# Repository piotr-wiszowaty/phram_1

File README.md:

phram\_1
========

phram\_1 is a Commodore Amiga A600 extension - 8 MB of fast RAM.

Features :
----------

* based on modern parts (CoolRunner CPLD, SDRAM)
* PCMCIA-friendly: holding `reset` for more than 3 seconds turns off high 4 MB
* current consumption around 110 mA
* speedup relative to stock A600: 33 % (by SysInfo)
* successfully tested with CheckMem and MemCheck 1.2 (both available
  on [Aminet](http://aminet.net)).

Sources
-------

`cpld/` - MMU design files (Xilinx ISE 14.7)

`pcb/`  - PCB design files (KiCAD, built 2017-11-24 revision a01d81e4b)

`prod/` - JED, Gerbers and a photo of the expansion; the current PCB
          has some tweaks compared with the device on the photo

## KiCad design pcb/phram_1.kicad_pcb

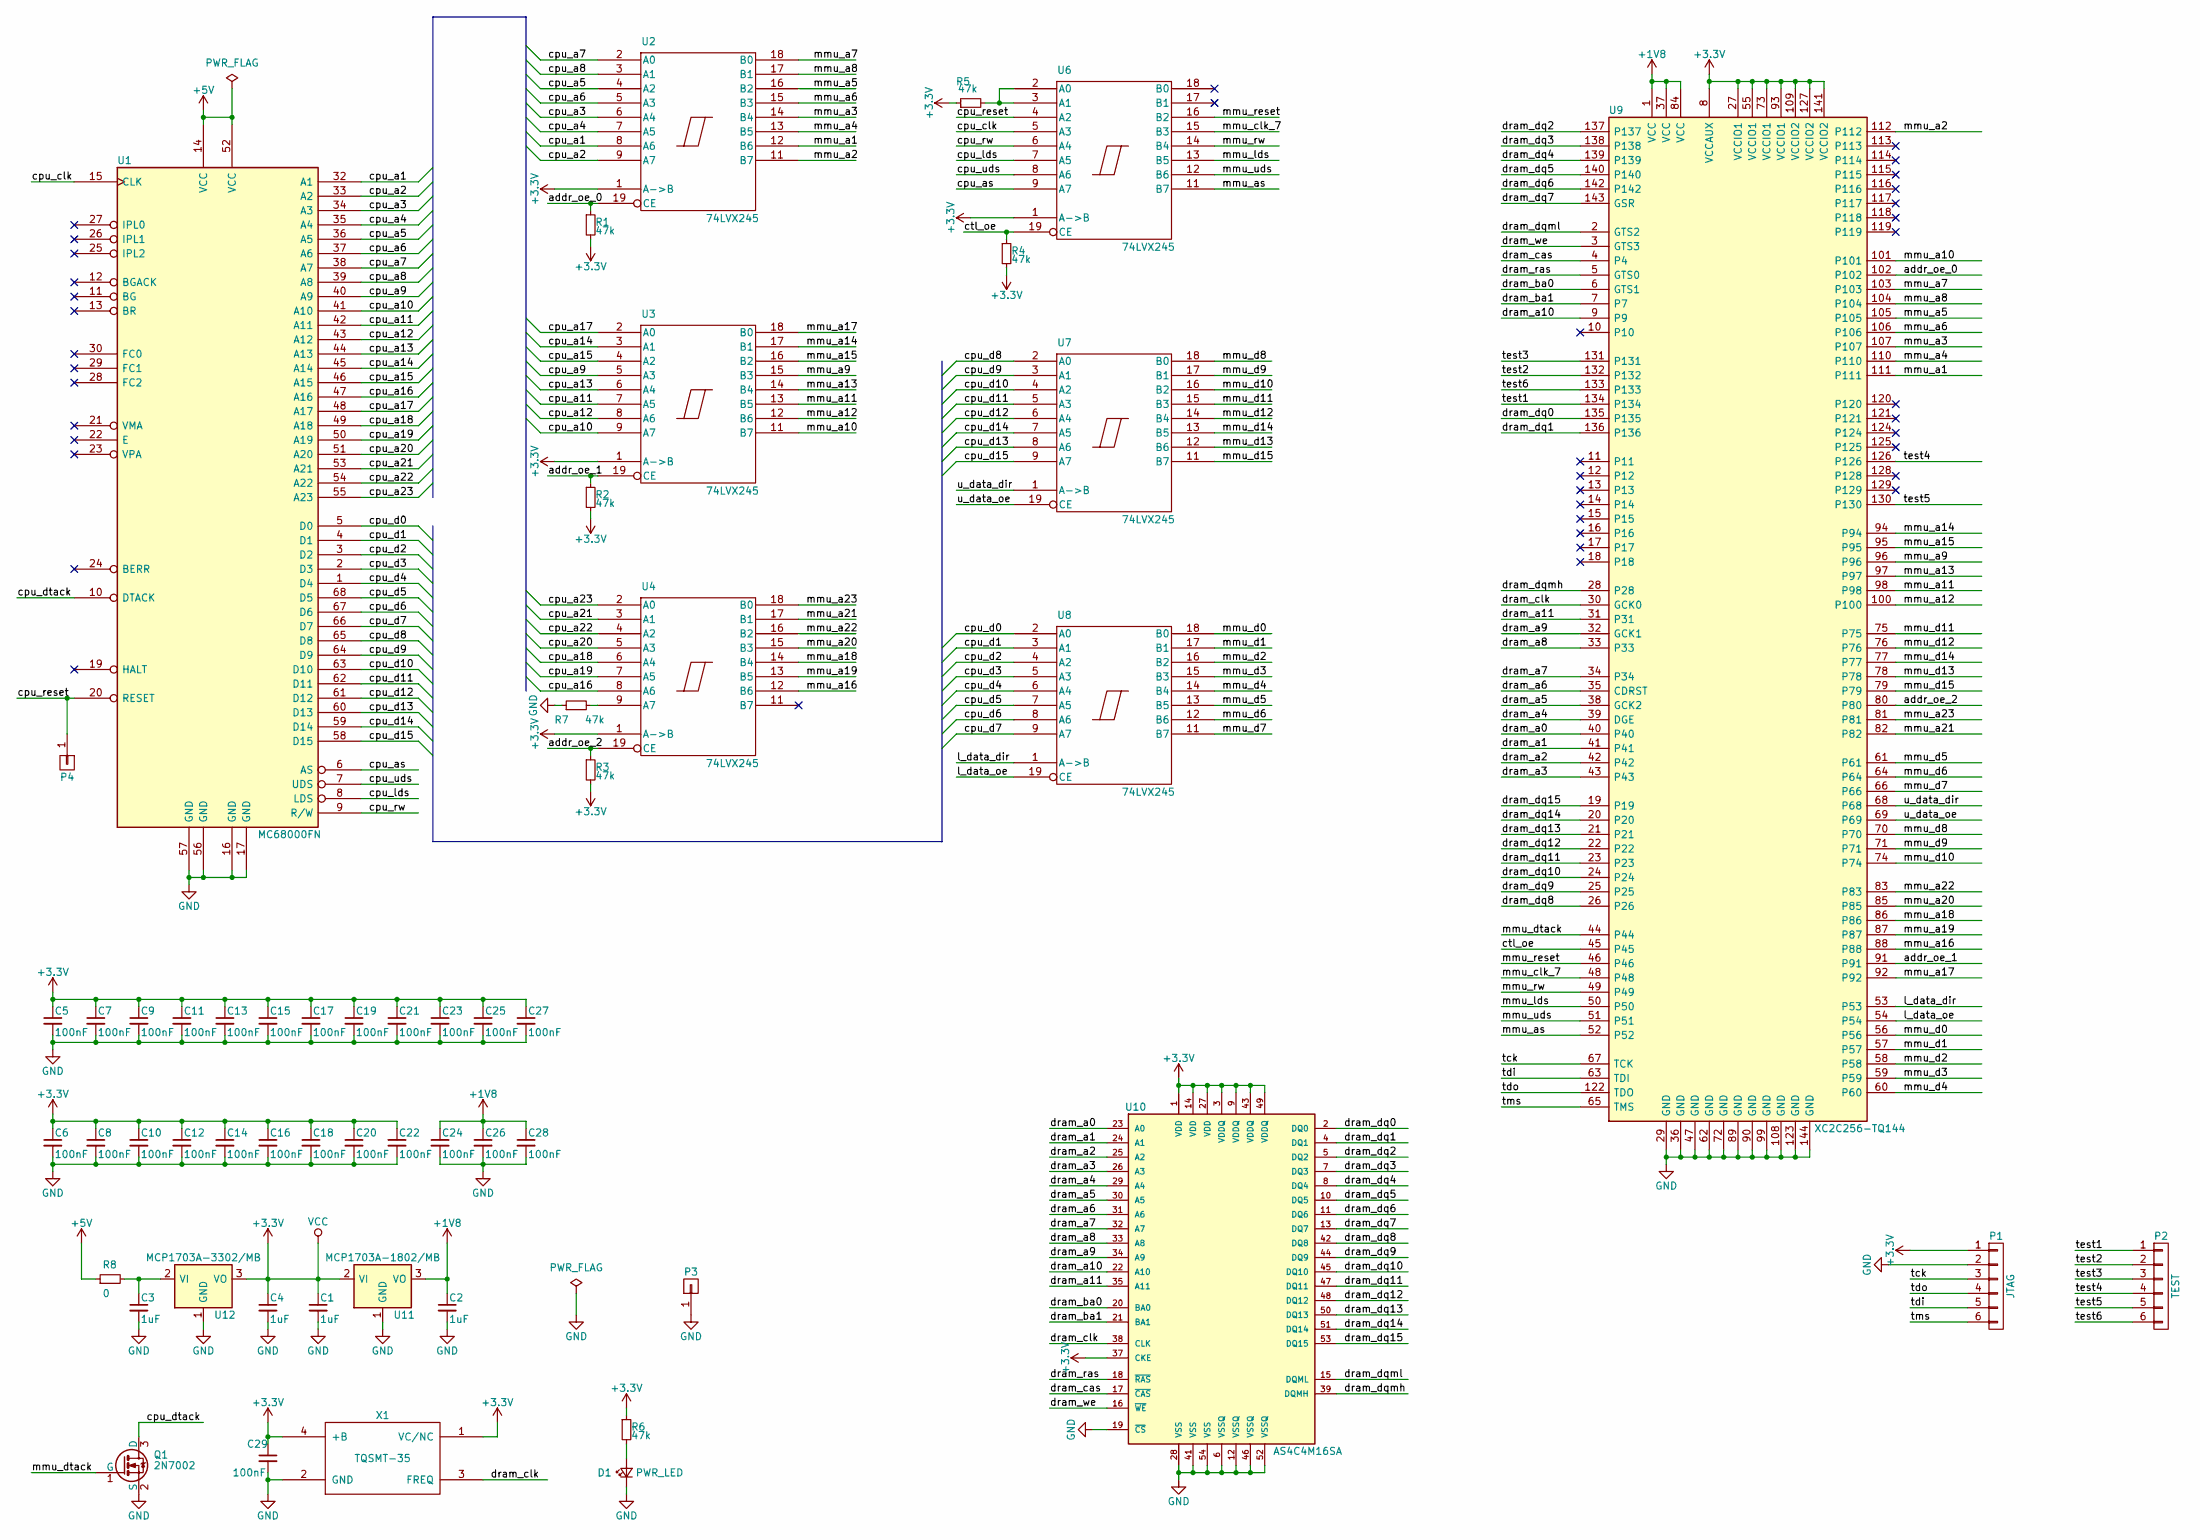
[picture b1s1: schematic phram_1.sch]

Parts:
C1, C2, C3, C4: 1uF; C_1206_HandSoldering
C5, C6, C7, C8, C9, C10, C11, C12, C13, C14, C15, C16, C17, C18, C19, C20, C21, C22, C23, C24, C25, C26, C27, C28, C29: 100nF; C_0805_HandSoldering
D1: PWR_LED; R_0805_HandSoldering
P1: JTAG; Pin_Header_Angled_1x06
P2: TEST; Pin_Header_Angled_1x06
P3, P4: CONN_01X01; Pin_Header_Straight_1x01
Q1: 2N7002; SOT-23
R1, R2, R3, R4, R5, R6, R7: 47k; R_0805_HandSoldering
R8: 0; R_1206_HandSoldering
U1: MC68000FN; PLCC68-upsidedown
U2, U3, U4, U6, U7, U8: 74LVX245; TSSOP-20_4.4x6.5mm_Pitch0.65mm
U9: XC2C256-TQ144; TQFP-144_20x20mm_Pitch0.5mm
U10: AS4C4M16SA; TSOP-II-54_22.22x10.16mm_Pitch0.8mm
U11: MCP1703A-1802/MB; SOT89-3_Housing
U12: MCP1703A-3302/MB; SOT89-3_Housing
X1: TQSMT-35; IS92

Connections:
+1V8: C2.1, C24.1, C26.1, C28.1, U9.1 (VCC), U9.37 (VCC), U9.84 (VCC), U11.3 (VO)
+3V3: C1.1, C4.1, C5.1, C6.1, C7.1, C8.1, C9.1, C10.1, C11.1, C12.1, C13.1, C14.1, C15.1, C16.1, C17.1, C18.1, C19.1, C20.1, C21.1, C22.1, C23.1, C25.1, C27.1, C29.1, P1.1, R1.2, R2.2, R3.2, R4.2, R5.1, R6.1, U2.1 (A->B), U2.20 (VCC), U3.1 (A->B), U3.20 (VCC), U4.1 (A->B), U4.20 (VCC), U6.1 (A->B), U6.20 (VCC), U7.20 (VCC), U8.20 (VCC), U9.8 (VCCAUX), U9.27 (VCCIO1), U9.55 (VCCIO1), U9.73 (VCCIO1), U9.93 (VCCIO1), U9.109 (VCCIO2), U9.127 (VCCIO2), U9.141 (VCCIO2), U10.1 (VDD), U10.3 (VDDQ), U10.9 (VDDQ), U10.14 (VDD), U10.27 (VDD), U10.37 (CKE), U10.43 (VDDQ), U10.49 (VDDQ), U11.2 (VI), U12.3 (VO), X1.1 (VC/NC), X1.4 (+B)
+5V: R8.1, U1.14 (VCC), U1.52 (VCC)
/addr_oe_0: R1.1, U2.19 (CE), U9.102
/addr_oe_1: R2.1, U3.19 (CE), U9.91
/addr_oe_2: R3.1, U4.19 (CE), U9.80
/cpu_a1: U1.32 (A1), U2.8 (A6)
/cpu_a2: U1.33 (A2), U2.9 (A7)
/cpu_a3: U1.34 (A3), U2.6 (A4)
/cpu_a4: U1.35 (A4), U2.7 (A5)
/cpu_a5: U1.36 (A5), U2.4 (A2)
/cpu_a6: U1.37 (A6), U2.5 (A3)
/cpu_a7: U1.38 (A7), U2.2 (A0)
/cpu_a8: U1.39 (A8), U2.3 (A1)
/cpu_a9: U1.40 (A9), U3.5 (A3)
/cpu_a10: U1.41 (A10), U3.9 (A7)
/cpu_a11: U1.42 (A11), U3.7 (A5)
/cpu_a12: U1.43 (A12), U3.8 (A6)
/cpu_a13: U1.44 (A13), U3.6 (A4)
/cpu_a14: U1.45 (A14), U3.3 (A1)
/cpu_a15: U1.46 (A15), U3.4 (A2)
/cpu_a16: U1.47 (A16), U4.8 (A6)
/cpu_a17: U1.48 (A17), U3.2 (A0)
/cpu_a18: U1.49 (A18), U4.6 (A4)
/cpu_a19: U1.50 (A19), U4.7 (A5)
/cpu_a20: U1.51 (A20), U4.5 (A3)
/cpu_a21: U1.53 (A21), U4.3 (A1)
/cpu_a22: U1.54 (A22), U4.4 (A2)
/cpu_a23: U1.55 (A23), U4.2 (A0)
/cpu_as: U1.6 (AS), U6.9 (A7)
/cpu_clk: U1.15 (CLK), U6.5 (A3)
/cpu_d0: U1.5 (D0), U8.2 (A0)
/cpu_d1: U1.4 (D1), U8.3 (A1)
/cpu_d2: U1.3 (D2), U8.4 (A2)
/cpu_d3: U1.2 (D3), U8.5 (A3)
/cpu_d4: U1.1 (D4), U8.6 (A4)
/cpu_d5: U1.68 (D5), U8.7 (A5)
/cpu_d6: U1.67 (D6), U8.8 (A6)
/cpu_d7: U1.66 (D7), U8.9 (A7)
/cpu_d8: U1.65 (D8), U7.2 (A0)
/cpu_d9: U1.64 (D9), U7.3 (A1)
/cpu_d10: U1.63 (D10), U7.4 (A2)
/cpu_d11: U1.62 (D11), U7.5 (A3)
/cpu_d12: U1.61 (D12), U7.6 (A4)
/cpu_d13: U1.60 (D13), U7.8 (A6)
/cpu_d14: U1.59 (D14), U7.7 (A5)
/cpu_d15: U1.58 (D15), U7.9 (A7)
/cpu_dtack: Q1.3 (D), U1.10 (DTACK)
/cpu_lds: U1.8 (LDS), U6.7 (A5)
/cpu_reset: P4.1, U1.20 (RESET), U6.4 (A2)
/cpu_rw: U1.9 (R/W), U6.6 (A4)
/cpu_uds: U1.7 (UDS), U6.8 (A6)
/ctl_oe: R4.1, U6.19 (CE), U9.45
/dram_a0: U9.40, U10.23 (A0)
/dram_a1: U9.41, U10.24 (A1)
/dram_a2: U9.42, U10.25 (A2)
/dram_a3: U9.43, U10.26 (A3)
/dram_a4: U9.39 (DGE), U10.29 (A4)
/dram_a5: U9.38 (GCK2), U10.30 (A5)
/dram_a6: U9.35 (CDRST), U10.31 (A6)
/dram_a7: U9.34, U10.32 (A7)
/dram_a8: U9.33, U10.33 (A8)
/dram_a9: U9.32 (GCK1), U10.34 (A9)
/dram_a10: U9.9, U10.22 (A10)
/dram_a11: U9.31, U10.35 (A11)
/dram_ba0: U9.6 (GTS1), U10.20 (BA0)
/dram_ba1: U9.7, U10.21 (BA1)
/dram_cas: U9.4, U10.17 (~CAS~)
/dram_clk: U9.30 (GCK0), U10.38 (CLK), X1.3 (FREQ)
/dram_dq0: U9.135, U10.2 (DQ0)
/dram_dq1: U9.136, U10.4 (DQ1)
/dram_dq2: U9.137, U10.5 (DQ2)
/dram_dq3: U9.138, U10.7 (DQ3)
/dram_dq4: U9.139, U10.8 (DQ4)
/dram_dq5: U9.140, U10.10 (DQ5)
/dram_dq6: U9.142, U10.11 (DQ6)
/dram_dq7: U9.143 (GSR), U10.13 (DQ7)
/dram_dq8: U9.26, U10.42 (DQ8)
/dram_dq9: U9.25, U10.44 (DQ9)
/dram_dq10: U9.24, U10.45 (DQ10)
/dram_dq11: U9.23, U10.47 (DQ11)
/dram_dq12: U9.22, U10.48 (DQ12)
/dram_dq13: U9.21, U10.50 (DQ13)
/dram_dq14: U9.20, U10.51 (DQ14)
/dram_dq15: U9.19, U10.53 (DQ15)
/dram_dqmh: U9.28, U10.39 (DQMH)
/dram_dqml: U9.2 (GTS2), U10.15 (DQML)
/dram_ras: U9.5 (GTS0), U10.18 (~RAS~)
/dram_we: U9.3 (GTS3), U10.16 (~WE~)
/l_data_dir: U8.1 (A->B), U9.53
/l_data_oe: U8.19 (CE), U9.54
/mmu_a1: U2.12 (B6), U9.111
/mmu_a2: U2.11 (B7), U9.112
/mmu_a3: U2.14 (B4), U9.107
/mmu_a4: U2.13 (B5), U9.110
/mmu_a5: U2.16 (B2), U9.105
/mmu_a6: U2.15 (B3), U9.106
/mmu_a7: U2.18 (B0), U9.103
/mmu_a8: U2.17 (B1), U9.104
/mmu_a9: U3.15 (B3), U9.96
/mmu_a10: U3.11 (B7), U9.101
/mmu_a11: U3.13 (B5), U9.98
/mmu_a12: U3.12 (B6), U9.100
/mmu_a13: U3.14 (B4), U9.97
/mmu_a14: U3.17 (B1), U9.94
/mmu_a15: U3.16 (B2), U9.95
/mmu_a16: U4.12 (B6), U9.88
/mmu_a17: U3.18 (B0), U9.92
/mmu_a18: U4.14 (B4), U9.86
/mmu_a19: U4.13 (B5), U9.87
/mmu_a20: U4.15 (B3), U9.85
/mmu_a21: U4.17 (B1), U9.82
/mmu_a22: U4.16 (B2), U9.83
/mmu_a23: U4.18 (B0), U9.81
/mmu_as: U6.11 (B7), U9.52
/mmu_clk_7: U6.15 (B3), U9.48
/mmu_d0: U8.18 (B0), U9.56
/mmu_d1: U8.17 (B1), U9.57
/mmu_d2: U8.16 (B2), U9.58
/mmu_d3: U8.15 (B3), U9.59
/mmu_d4: U8.14 (B4), U9.60
/mmu_d5: U8.13 (B5), U9.61
/mmu_d6: U8.12 (B6), U9.64
/mmu_d7: U8.11 (B7), U9.66
/mmu_d8: U7.18 (B0), U9.70
/mmu_d9: U7.17 (B1), U9.71
/mmu_d10: U7.16 (B2), U9.74
/mmu_d11: U7.15 (B3), U9.75
/mmu_d12: U7.14 (B4), U9.76
/mmu_d13: U7.12 (B6), U9.78
/mmu_d14: U7.13 (B5), U9.77
/mmu_d15: U7.11 (B7), U9.79
/mmu_dtack: Q1.1 (G), U9.44
/mmu_lds: U6.13 (B5), U9.50
/mmu_reset: U6.16 (B2), U9.46
/mmu_rw: U6.14 (B4), U9.49
/mmu_uds: U6.12 (B6), U9.51
/tck: P1.3, U9.67 (TCK)
/tdi: P1.5, U9.63 (TDI)
/tdo: P1.4, U9.122 (TDO)
/test1: P2.1, U9.134
/test2: P2.2, U9.132
/test3: P2.3, U9.131
/test4: P2.4, U9.126
/test5: P2.5, U9.130
/test6: P2.6, U9.133
/tms: P1.6, U9.65 (TMS)
/u_data_dir: U7.1 (A->B), U9.68
/u_data_oe: U7.19 (CE), U9.69
GND: C1.2, C2.2, C3.2, C4.2, C5.2, C6.2, C7.2, C8.2, C9.2, C10.2, C11.2, C12.2, C13.2, C14.2, C15.2, C16.2, C17.2, C18.2, C19.2, C20.2, C21.2, C22.2, C23.2, C24.2, C25.2, C26.2, C27.2, C28.2, C29.2, D1.1 (K), P1.2, P3.1, Q1.2 (S), R7.1, U1.16 (GND), U1.17 (GND), U1.56 (GND), U1.57 (GND), U2.10 (GND), U3.10 (GND), U4.10 (GND), U6.10 (GND), U7.10 (GND), U8.10 (GND), U9.29 (GND), U9.36 (GND), U9.47 (GND), U9.62 (GND), U9.72 (GND), U9.89 (GND), U9.90 (GND), U9.99 (GND), U9.108 (GND), U9.123 (GND), U9.144 (GND), U10.6 (VSSQ), U10.12 (VSSQ), U10.19 (~CS~), U10.28 (VSS), U10.41 (VSS), U10.46 (VSSQ), U10.52 (VSSQ), U10.54 (VSS), U11.1 (GND), U12.1 (GND), X1.2 (GND)
unnamed: C3.1, R8.2, U12.2 (VI)
unnamed: D1.2 (A), R6.2
unnamed: R5.2, U6.2 (A0), U6.3 (A1)
unnamed: R7.2, U4.9 (A7)

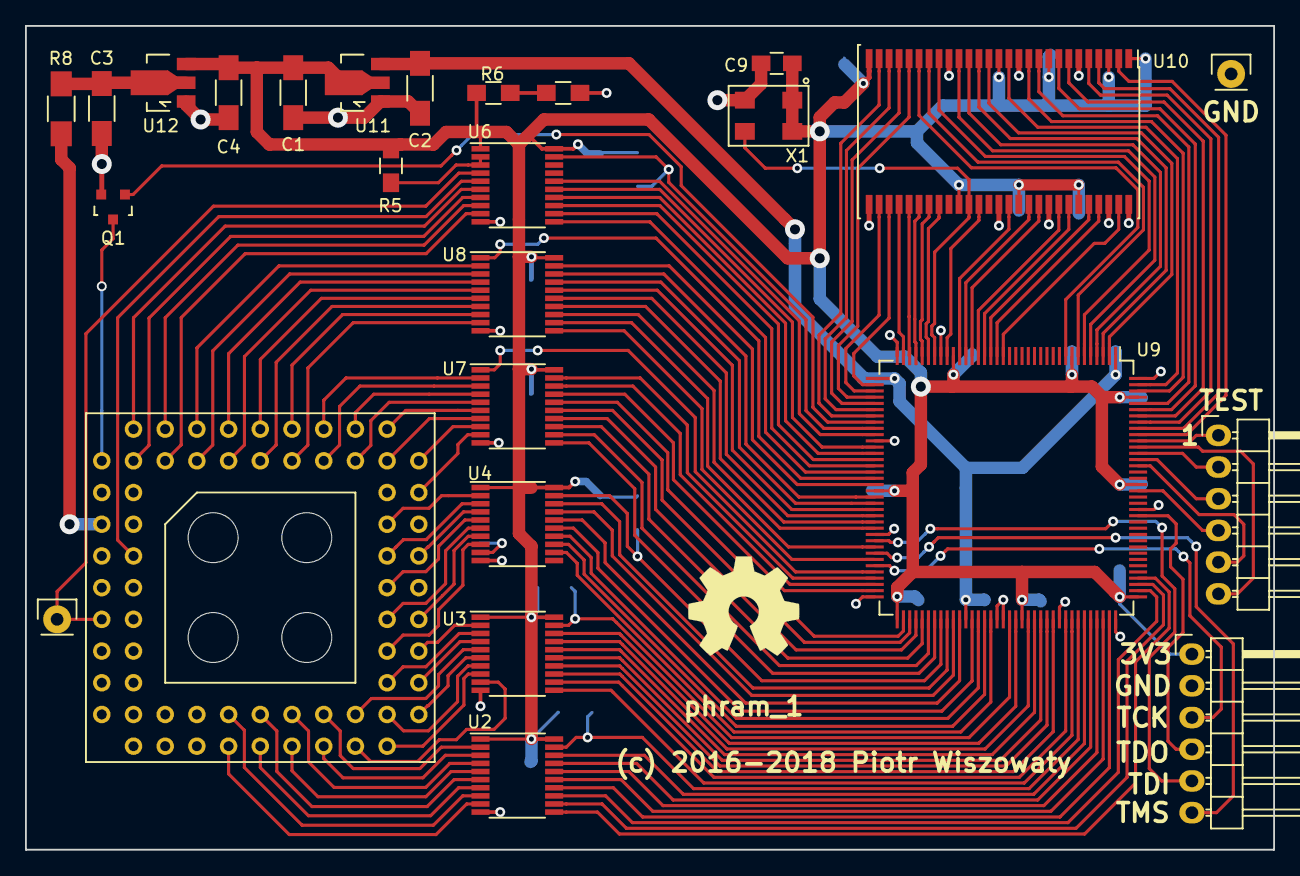
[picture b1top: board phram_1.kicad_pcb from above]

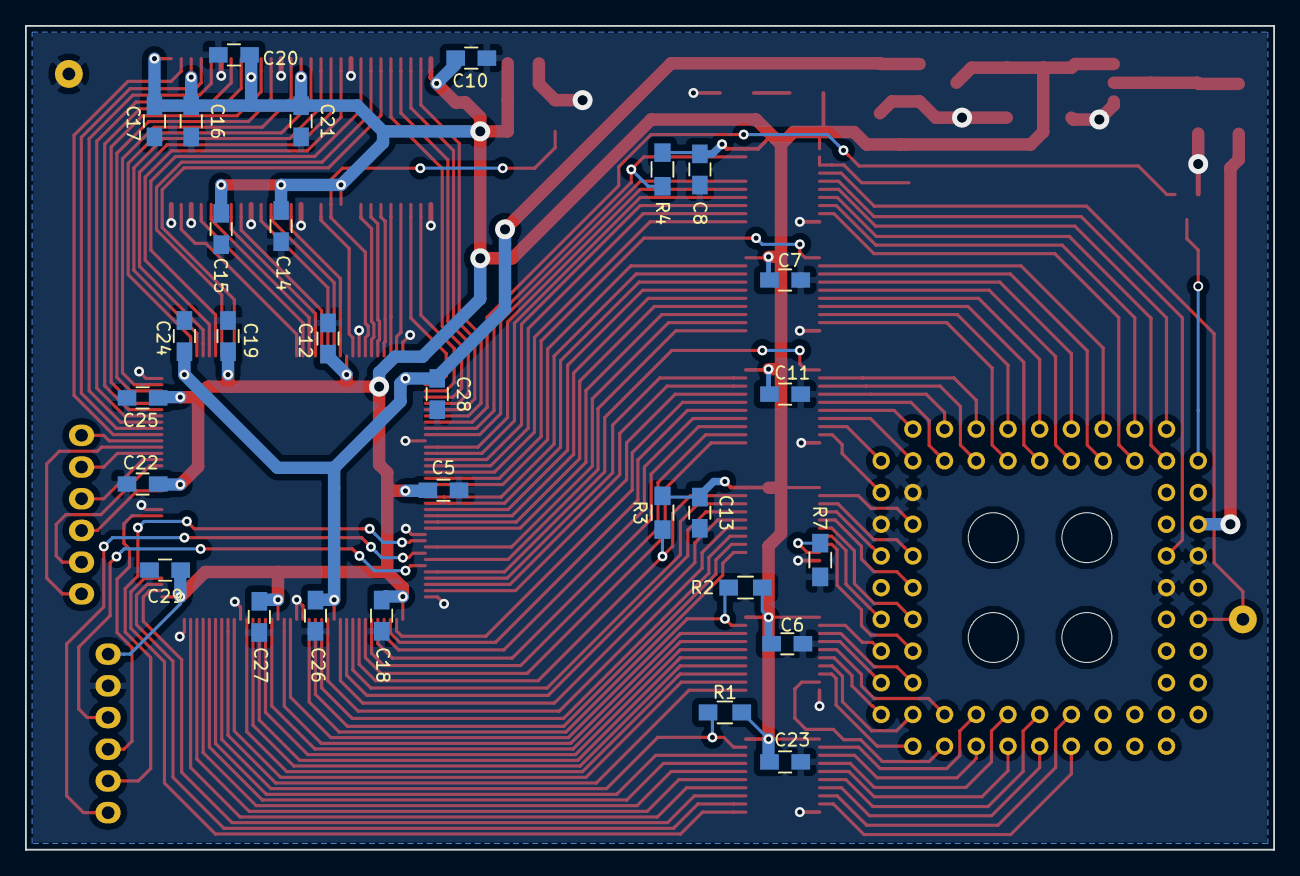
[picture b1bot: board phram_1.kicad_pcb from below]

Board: 2 copper layers, 100.0 x 66.0 mm, 55 parts (29 on the bottom side), 154 nets.

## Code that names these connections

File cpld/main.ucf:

NET "dram_clk" TNM = dram_clk;
TIMESPEC TS_clk = PERIOD "dram_clk" 50.0 MHz HIGH 50%;
NET "dram_clk" BUFG = CLK;

NET "mmu_clk_7" TNM = mmu_clk_7;
TIMESPEC TS_ami_clk = PERIOD "mmu_clk_7" 7.2 MHz HIGH 50%;

NET "mmu_data<0>" LOC = p56;
NET "mmu_data<1>" LOC = p57;
NET "mmu_data<2>" LOC = p58;
NET "mmu_data<3>" LOC = p59;
NET "mmu_data<4>" LOC = p60;
NET "mmu_data<5>" LOC = p61;
NET "mmu_data<6>" LOC = p64;
NET "mmu_data<7>" LOC = p66;
NET "mmu_data<8>" LOC = p70;
NET "mmu_data<9>" LOC = p71;
NET "mmu_data<10>" LOC = p74;
NET "mmu_data<11>" LOC = p75;
NET "mmu_data<12>" LOC = p76;
NET "mmu_data<13>" LOC = p78;
NET "mmu_data<14>" LOC = p77;
NET "mmu_data<15>" LOC = p79;
NET "mmu_addr<1>" LOC = p111;
NET "mmu_addr<2>" LOC = p112;
NET "mmu_addr<3>" LOC = p107;
NET "mmu_addr<4>" LOC = p110;
NET "mmu_addr<5>" LOC = p105;
NET "mmu_addr<6>" LOC = p106;
NET "mmu_addr<7>" LOC = p103;
NET "mmu_addr<8>" LOC = p104;
NET "mmu_addr<9>" LOC = p96;
NET "mmu_addr<10>" LOC = p101;
NET "mmu_addr<11>" LOC = p98;
NET "mmu_addr<12>" LOC = p100;
NET "mmu_addr<13>" LOC = p97;
NET "mmu_addr<14>" LOC = p94;
NET "mmu_addr<15>" LOC = p95;
NET "mmu_addr<16>" LOC = p88;
NET "mmu_addr<17>" LOC = p92;
NET "mmu_addr<18>" LOC = p86;
NET "mmu_addr<19>" LOC = p87;
NET "mmu_addr<20>" LOC = p85;
NET "mmu_addr<21>" LOC = p82;
NET "mmu_addr<22>" LOC = p83;
NET "mmu_addr<23>" LOC = p81;

NET "mmu_dtack" LOC = p44;
NET "mmu_reset" LOC = p46;
NET "mmu_clk_7" LOC = p48;
NET "mmu_rw" LOC = p49;
NET "mmu_lds" LOC = p50;
NET "mmu_uds" LOC = p51;
NET "mmu_as" LOC = p52;

NET "ctl_oe" LOC = p45;
NET "l_data_oe" LOC = p54;
NET "u_data_oe" LOC = p69;
NET "l_data_dir" LOC = p53;
NET "u_data_dir" LOC = p68;
NET "addr_oe_0" LOC = p102;
NET "addr_oe_1" LOC = p91;
NET "addr_oe_2" LOC = p80;

NET "dram_addr<0>" LOC = p40;
NET "dram_addr<1>" LOC = p41;
NET "dram_addr<2>" LOC = p42;
NET "dram_addr<3>" LOC = p43;
NET "dram_addr<4>" LOC = p39;
NET "dram_addr<5>" LOC = p38;
NET "dram_addr<6>" LOC = p35;
NET "dram_addr<7>" LOC = p34;
NET "dram_addr<8>" LOC = p33;
NET "dram_addr<9>" LOC = p32;
NET "dram_addr<10>" LOC = p9;
NET "dram_addr<11>" LOC = p31;
NET "dram_dq<0>" LOC = p135;
NET "dram_dq<1>" LOC = p136;
NET "dram_dq<2>" LOC = p137;
NET "dram_dq<3>" LOC = p138;
NET "dram_dq<4>" LOC = p139;
NET "dram_dq<5>" LOC = p140;
NET "dram_dq<6>" LOC = p142;
NET "dram_dq<7>" LOC = p143;
NET "dram_dq<8>" LOC = p26;
NET "dram_dq<9>" LOC = p25;
NET "dram_dq<10>" LOC = p24;
NET "dram_dq<11>" LOC = p23;
NET "dram_dq<12>" LOC = p22;
NET "dram_dq<13>" LOC = p21;
NET "dram_dq<14>" LOC = p20;
NET "dram_dq<15>" LOC = p19;
NET "dram_ba<0>" LOC = p6;
NET "dram_ba<1>" LOC = p7;
NET "dram_dqml" LOC = p2;
NET "dram_dqmh" LOC = p28;
NET "dram_ras_n" LOC = p5;
NET "dram_cas_n" LOC = p4;
NET "dram_we_n" LOC = p3;
NET "dram_clk" LOC = p30;

NET "test<1>" LOC = p134;
NET "test<2>" LOC = p132;
NET "test<3>" LOC = p131;
NET "test<4>" LOC = p126;
NET "test<5>" LOC = p130;
NET "test<6>" LOC = p133;

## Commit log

2018-01-27 Add CPLD and PCB design files, update README
2018-01-27 Add JED, Gerbers and a photo

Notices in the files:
pcb/phram_1.kicad_pcb:
(c) 2016-2018 Piotr Wiszowaty
